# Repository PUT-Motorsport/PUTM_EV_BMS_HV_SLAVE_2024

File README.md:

# PUTM_EV_BMS_HV_SLAVE_2024
Accumulator Managment System (High Voltage Battery Managment System)

## Overview
The AMS system consists of two main parts, the master and multiple slaves.

The apparatus is responsible for the managment of the battery as a whole, determining it's states like: state of charge or unsafe state plausibility. It also supervises the turning on and off of the hv bus.

## Slave
The AMS Slave is a subsidiary system responsible for measuring all the cell voltages and strategically placed temperatures on one stack.

### Hardware 
The AMS Slave is powered by LTC6811, a powerful, new gen IC capable of measuring of up to 12 cell simultaneously and up to 5 auxilary readings. One slave features 2 of such IC for a total of 20 cell and 10 temperature measurements. All Slaves are connected in chain configuration allowing for a quick data dump from all slaves in series. For interfacing the LTC6811 uses isoSPI, a special SPI/Ethernet like protocol, which features amazing noise immunity due to usage of a twisted differential pair. All of that on a custom 4 layer board. The AMS slave boasts a lot smaller (106mm x 50mm) size compared to it's predecessor allowing for a lot more versatile usage and making one cell stack far more compact. 

### The research and development work was carried out was a part of the Student Scientific Clubs Create Innovations (SKNTI) program. [Ministry of Science and Higher Education](https://www.gov.pl/web/nauka)

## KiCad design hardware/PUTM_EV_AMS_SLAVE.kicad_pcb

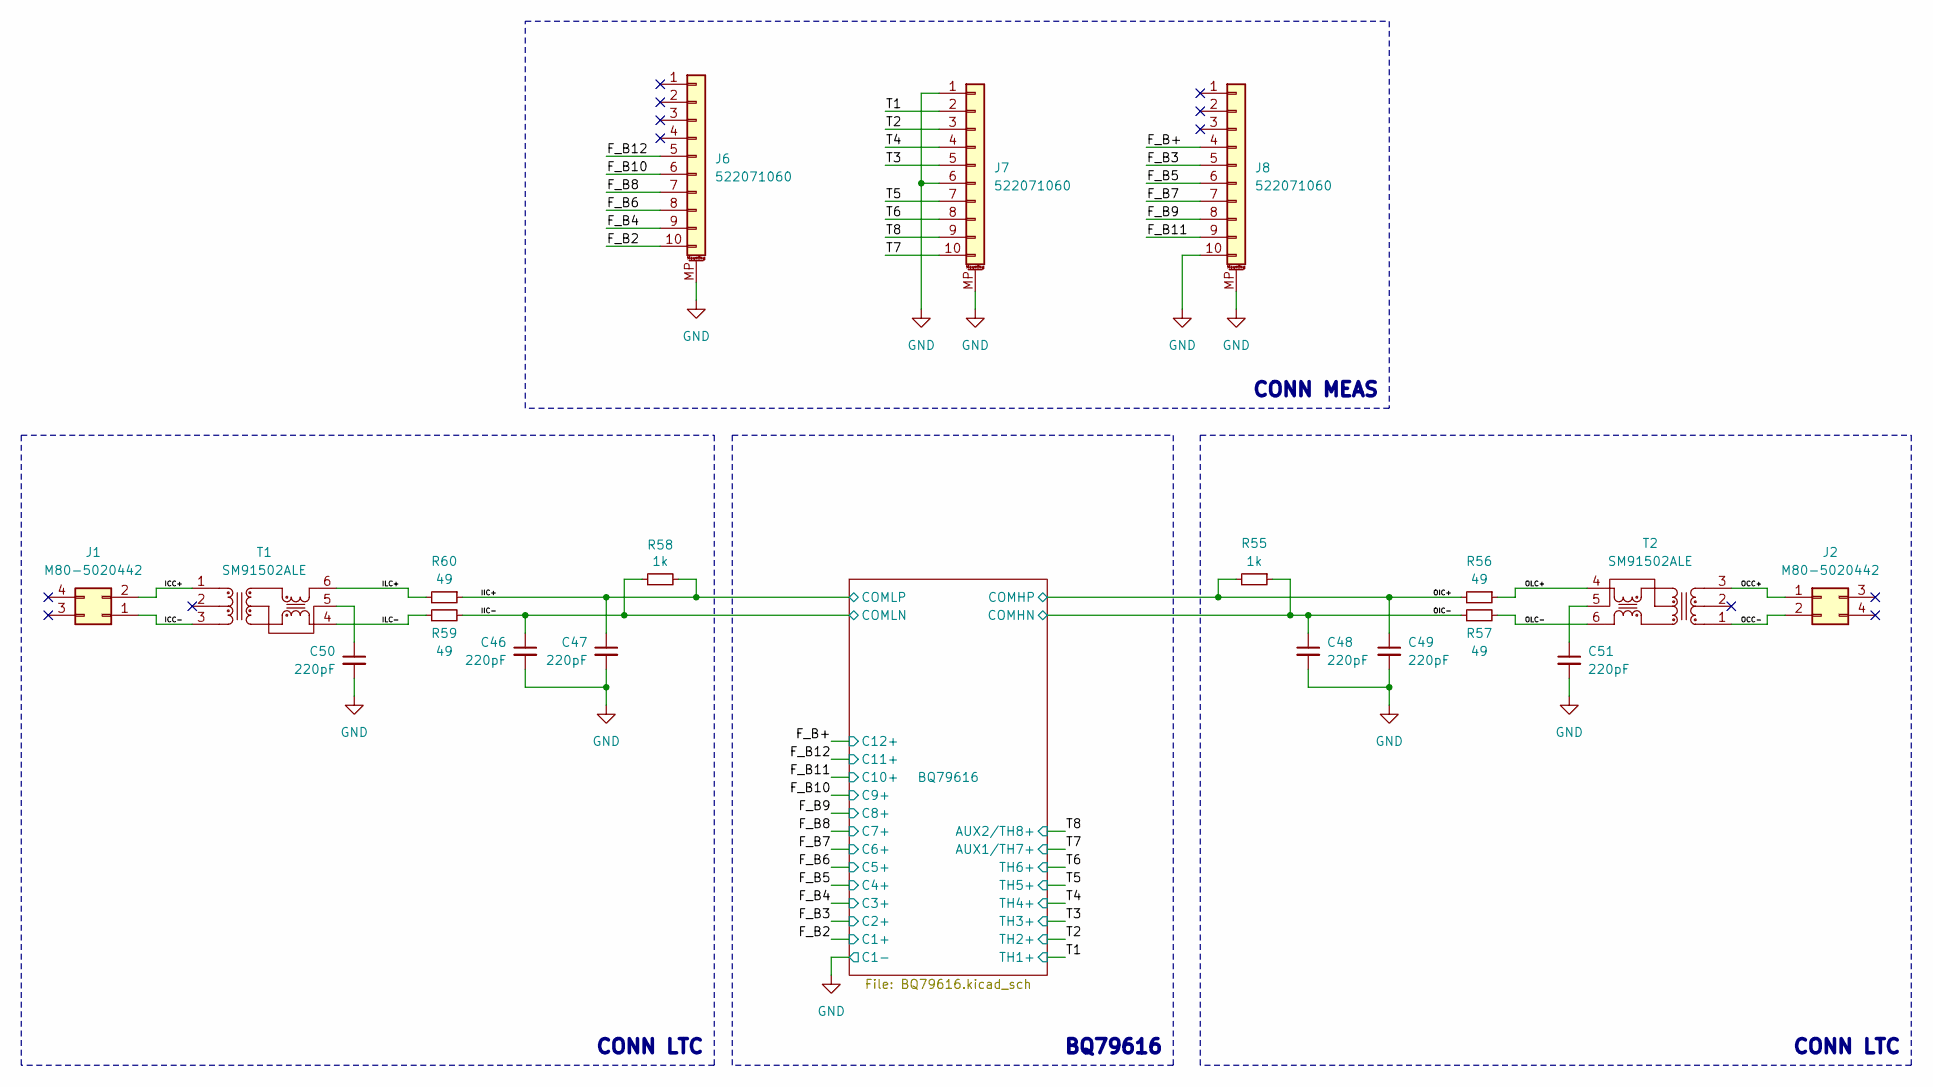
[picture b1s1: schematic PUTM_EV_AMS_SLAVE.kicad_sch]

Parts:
C46, C47, C48, C49, C50, C51: 220pF; C_0603_1608Metric; Mouser Part Number 581-06033A221JAT2A
J1, J2: M80-5020442; M80-50204YY; Mouser Part Number 855-M80-5020442
J6, J7, J8: 522071060; Mouser Part Number 538-52207-1060
R55, R58: 1k; R_0603_1608Metric; Manufacturer_Part_Number RT0603FRE07330RL; Mouser Part Number --
R56, R57, R59, R60: 49; R_0603_1608Metric; Manufacturer_Part_Number RT0603FRE07330RL; Mouser Part Number 603-RT0603FRE07330RL
T1, T2: SM91502ALE; SOP254P927X572-6N; Mouser Part Number 652-SM91502ALE

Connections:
/F_B2: J6.10; also elsewhere on the board
/F_B3: J8.5; also elsewhere on the board
/F_B4: J6.9; also elsewhere on the board
/F_B5: J8.6; also elsewhere on the board
/F_B6: J6.8; also elsewhere on the board
/F_B7: J8.7; also elsewhere on the board
/F_B8: J6.7; also elsewhere on the board
/F_B9: J8.8; also elsewhere on the board
/F_B10: J6.6; also elsewhere on the board
/F_B11: J8.9; also elsewhere on the board
/F_B12: J6.5; also elsewhere on the board
/F_B+: J8.4; also elsewhere on the board
/ICC+: J1.2, T1.1 (PRI_1)
/ICC-: J1.1, T1.3 (PRI_3)
/IIC+: C47.1, R58.2, R60.1; also elsewhere on the board
/IIC-: C46.1, R58.1, R59.2; also elsewhere on the board
/ILC+: R60.2, T1.6 (SEC_3)
/ILC-: R59.1, T1.4 (SEC_1)
/OCC+: J2.1, T2.3 (PRI_3)
/OCC-: J2.2, T2.1 (PRI_1)
/OIC+: C49.1, R55.2, R56.2; also elsewhere on the board
/OIC-: C48.1, R55.1, R57.1; also elsewhere on the board
/OLC+: R56.1, T2.4 (SEC_1)
/OLC-: R57.2, T2.6 (SEC_3)
/T1: J7.2; also elsewhere on the board
/T2: J7.3; also elsewhere on the board
/T3: J7.5; also elsewhere on the board
/T4: J7.4; also elsewhere on the board
/T5: J7.7; also elsewhere on the board
/T6: J7.8; also elsewhere on the board
/T7: J7.10; also elsewhere on the board
/T8: J7.9; also elsewhere on the board
GND: C46.2, C47.2, C48.2, C49.2, C50.2, C51.2, J6.MP (MountPin), J7.1, J7.6, J7.MP (MountPin), J8.10, J8.MP (MountPin); also elsewhere on the board
unnamed: C50.1, T1.5 (SEC_2)
unnamed: C51.1, T2.5 (SEC_2)

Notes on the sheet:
BQ79616
CONN LTC
CONN MEAS

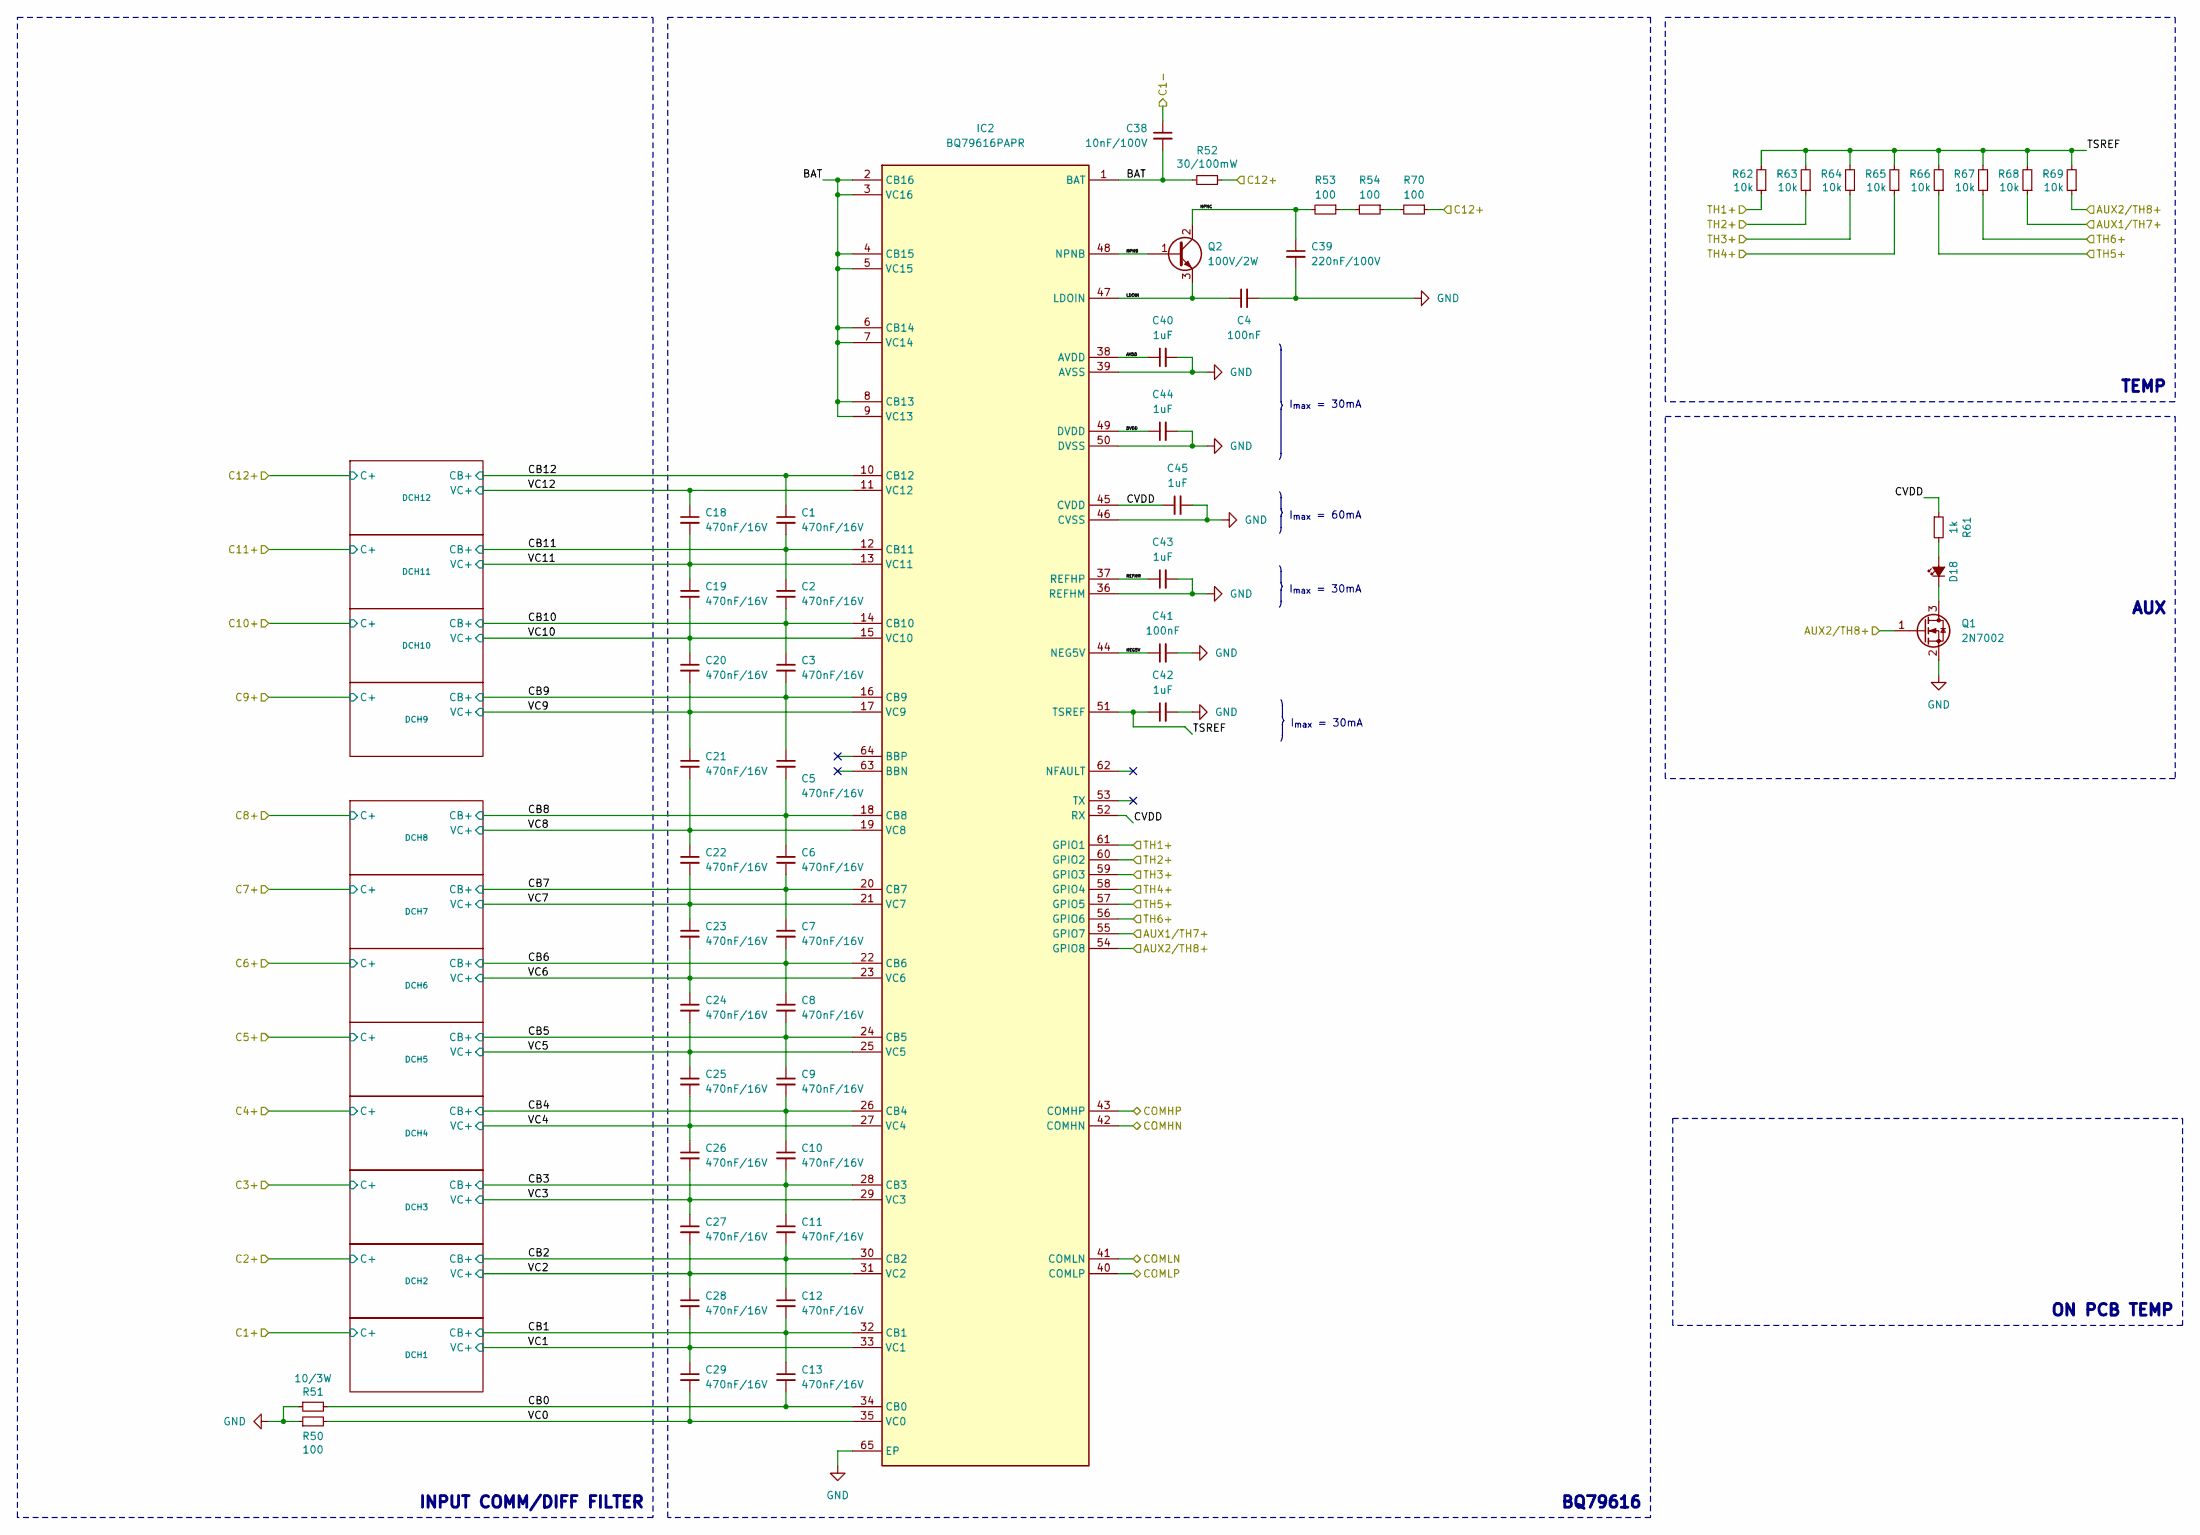
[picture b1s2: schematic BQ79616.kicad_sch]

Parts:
C1, C2, C3, C5, C6, C7, C8, C9, C10, C11, C12, C13, C18, C19, C20, C21, C22, C23, C24, C25, C26, C27, C28, C29: 470nF/16V; C_0603_1608Metric; Mouser Part Number 963-TMK107B7474KA-TR
C4, C41: 100nF; C_0603_1608Metric; Mouser Part Number --
C38: 10nF/100V; C_0603_1608Metric; Mouser Part Number 81-GRT188R72A103KE1J
C39: 220nF/100V; C_0805_2012Metric; Mouser Part Number 963-H168SC7224KTCA1J
C40, C42, C43, C44, C45: 1uF; C_0603_1608Metric; Mouser Part Number 187-CL10B105KA8NNNL
D18: LED; LED_0603_1608Metric; Manufacturer_Part_Number 150060SS75000; Mouser Part Number 710-150060SS75000
IC2: BQ79616PAPR; QFP50P1200X1200X120-65N; Mouser Part Number 595-BQ79616PAPR
Q1: 2N7002; SOT-23
Q2: 100V/2W; SOT-223-3_TabPin2; Mouser Part Number 522-FZT653TA
R50, R53, R54, R70: 100; R_0603_1608Metric; Manufacturer_Part_Number RT0603FRE07330RL; Mouser Part Number --
R51: 10/3W; R_2512_6332Metric; Manufacturer_Part_Number 352210RJT; Mouser Part Number 279-352210RJT
R52: 30/100mW; R_0603_1608Metric; Manufacturer_Part_Number RT0603FRE07330RL; Mouser Part Number 603-RT0603FRE07330RL
R61: 1k; R_0603_1608Metric; Manufacturer_Part_Number RT0603FRE07330RL; Mouser Part Number --
R62, R63, R64, R65, R66, R67, R68, R69: 10k; R_0603_1608Metric; Manufacturer_Part_Number RT0603FRE07330RL; Mouser Part Number --

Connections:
/BQ79616/AVDD: C40.1, IC2.38 (AVDD)
/BQ79616/BAT: C38.2, IC2.1 (BAT), IC2.2 (CB16), IC2.3 (VC16), IC2.4 (CB15), IC2.5 (VC15), IC2.6 (CB14), IC2.7 (VC14), IC2.8 (CB13), IC2.9 (VC13), R52.2
/BQ79616/CB0: C13.2, IC2.34 (CB0), R51.2
/BQ79616/CB1: C12.2, C13.1, IC2.32 (CB1); also elsewhere on the board
/BQ79616/CB2: C11.2, C12.1, IC2.30 (CB2); also elsewhere on the board
/BQ79616/CB3: C10.2, C11.1, IC2.28 (CB3); also elsewhere on the board
/BQ79616/CB4: C9.2, C10.1, IC2.26 (CB4); also elsewhere on the board
/BQ79616/CB5: C8.2, C9.1, IC2.24 (CB5); also elsewhere on the board
/BQ79616/CB6: C7.2, C8.1, IC2.22 (CB6); also elsewhere on the board
/BQ79616/CB7: C6.2, C7.1, IC2.20 (CB7); also elsewhere on the board
/BQ79616/CB8: C5.2, C6.1, IC2.18 (CB8); also elsewhere on the board
/BQ79616/CB9: C3.2, C5.1, IC2.16 (CB9); also elsewhere on the board
/BQ79616/CB10: C2.2, C3.1, IC2.14 (CB10); also elsewhere on the board
/BQ79616/CB11: C1.2, C2.1, IC2.12 (CB11); also elsewhere on the board
/BQ79616/CB12: C1.1, IC2.10 (CB12); also elsewhere on the board
/BQ79616/CVDD: C45.1, IC2.45 (CVDD), IC2.52 (RX), R61.1
/BQ79616/DVDD: C44.1, IC2.49 (DVDD)
/BQ79616/LDOIN: C4.1, IC2.47 (LDOIN), Q2.3 (E)
/BQ79616/NEG5V: C41.1, IC2.44 (NEG5V)
/BQ79616/NPNB: IC2.48 (NPNB), Q2.1 (B)
/BQ79616/NPNC: C39.1, Q2.2 (C), R53.2
/BQ79616/REFHM: C43.1, IC2.37 (REFHP)
/BQ79616/TSREF: C42.1, IC2.51 (TSREF), R62.2, R63.2, R64.2, R65.2, R66.2, R67.2, R68.2, R69.2
/BQ79616/VC0: C29.2, IC2.35 (VC0), R50.2
/BQ79616/VC1: C28.2, C29.1, IC2.33 (VC1); also elsewhere on the board
/BQ79616/VC2: C27.2, C28.1, IC2.31 (VC2); also elsewhere on the board
/BQ79616/VC3: C26.2, C27.1, IC2.29 (VC3); also elsewhere on the board
/BQ79616/VC4: C25.2, C26.1, IC2.27 (VC4); also elsewhere on the board
/BQ79616/VC5: C24.2, C25.1, IC2.25 (VC5); also elsewhere on the board
/BQ79616/VC6: C23.2, C24.1, IC2.23 (VC6); also elsewhere on the board
/BQ79616/VC7: C22.2, C23.1, IC2.21 (VC7); also elsewhere on the board
/BQ79616/VC8: C21.2, C22.1, IC2.19 (VC8); also elsewhere on the board
/BQ79616/VC9: C20.2, C21.1, IC2.17 (VC9); also elsewhere on the board
/BQ79616/VC10: C19.2, C20.1, IC2.15 (VC10); also elsewhere on the board
/BQ79616/VC11: C18.2, C19.1, IC2.13 (VC11); also elsewhere on the board
/BQ79616/VC12: C18.1, IC2.11 (VC12); also elsewhere on the board
/F_B+: R52.1, R70.1; also elsewhere on the board
/IIC+: IC2.40 (COMLP); also elsewhere on the board
/IIC-: IC2.41 (COMLN); also elsewhere on the board
/OIC+: IC2.43 (COMHP); also elsewhere on the board
/OIC-: IC2.42 (COMHN); also elsewhere on the board
/T1: IC2.61 (GPIO1), R62.1; also elsewhere on the board
/T2: IC2.60 (GPIO2), R63.1; also elsewhere on the board
/T3: IC2.59 (GPIO3), R64.1; also elsewhere on the board
/T4: IC2.58 (GPIO4), R65.1; also elsewhere on the board
/T5: IC2.57 (GPIO5), R66.1; also elsewhere on the board
/T6: IC2.56 (GPIO6), R67.1; also elsewhere on the board
/T7: IC2.55 (GPIO7), R68.1; also elsewhere on the board
/T8: IC2.54 (GPIO8), Q1.1 (G), R69.1; also elsewhere on the board
GND: C4.2, C38.1, C39.2, C40.2, C41.2, C42.2, C43.2, C44.2, C45.2, IC2.36 (REFHM), IC2.39 (AVSS), IC2.46 (CVSS), IC2.50 (DVSS), IC2.65 (EP), Q1.2 (S), R50.1, R51.1; also elsewhere on the board
unnamed: D18.2 (A), R61.2
unnamed: D18.1 (K), Q1.3 (D)
unnamed: R53.1, R54.2
unnamed: R54.1, R70.2

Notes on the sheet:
ON PCB TEMP
TEMP
BQ79616
AUX
I_{max} = 30mA
INPUT COMM/DIFF FILTER
I_{max} = 60mA

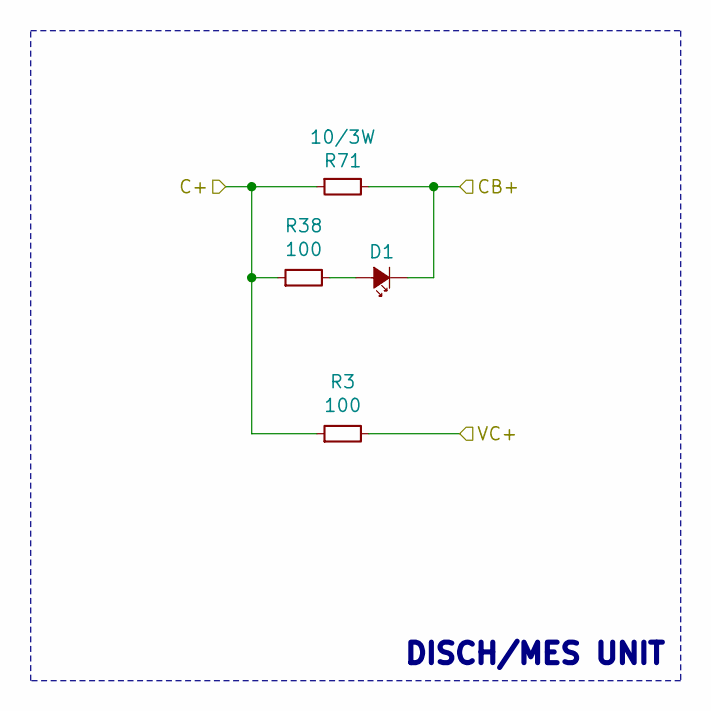
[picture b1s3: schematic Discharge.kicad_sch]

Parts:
D1: LED; LED_0603_1608Metric; Manufacturer_Part_Number 150060SS75000; Mouser Part Number 710-150060SS75000
R3, R38: 100; R_0603_1608Metric; Manufacturer_Part_Number RT0603FRE07330RL; Mouser Part Number --
R71: 10/3W; R_2512_6332Metric; Manufacturer_Part_Number 352210RJT; Mouser Part Number 279-352210RJT

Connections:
/BQ79616/CB1: D1.1 (K), R71.2; also elsewhere on the board
/BQ79616/VC1: R3.2; also elsewhere on the board
/F_B2: R3.1, R38.1, R71.1; also elsewhere on the board
unnamed: D1.2 (A), R38.2

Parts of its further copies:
D2, D3, D4, D5, D6, D7, D8, D9, D10, D11, D12: LED; LED_0603_1608Metric; Manufacturer_Part_Number 150060SS75000; Mouser Part Number 710-150060SS75000
R5, R8, R13, R16, R19, R22, R25, R28, R31, R34, R37, R39, R40, R41, R42, R43, R44, R45, R46, R47, R48, R49: 100; R_0603_1608Metric; Manufacturer_Part_Number RT0603FRE07330RL; Mouser Part Number --
R72, R73, R74, R75, R76, R77, R78, R79, R80, R81, R82: 10/3W; R_2512_6332Metric; Manufacturer_Part_Number 352210RJT; Mouser Part Number 279-352210RJT

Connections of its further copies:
/BQ79616/CB2: D2.1 (K), R72.2; also elsewhere on the board
/BQ79616/CB3: D3.1 (K), R73.2; also elsewhere on the board
/BQ79616/CB4: D4.1 (K), R74.2; also elsewhere on the board
/BQ79616/CB5: D5.1 (K), R75.2; also elsewhere on the board
/BQ79616/CB6: D6.1 (K), R76.2; also elsewhere on the board
/BQ79616/CB7: D7.1 (K), R77.2; also elsewhere on the board
/BQ79616/CB8: D8.1 (K), R78.2; also elsewhere on the board
/BQ79616/CB9: D9.1 (K), R79.2; also elsewhere on the board
/BQ79616/CB10: D10.1 (K), R80.2; also elsewhere on the board
/BQ79616/CB11: D11.1 (K), R81.2; also elsewhere on the board
/BQ79616/CB12: D12.1 (K), R82.2; also elsewhere on the board
/BQ79616/VC2: R5.2; also elsewhere on the board
/BQ79616/VC3: R8.2; also elsewhere on the board
/BQ79616/VC4: R13.2; also elsewhere on the board
/BQ79616/VC5: R16.2; also elsewhere on the board
/BQ79616/VC6: R19.2; also elsewhere on the board
/BQ79616/VC7: R22.2; also elsewhere on the board
/BQ79616/VC8: R25.2; also elsewhere on the board
/BQ79616/VC9: R28.2; also elsewhere on the board
/BQ79616/VC10: R31.2; also elsewhere on the board
/BQ79616/VC11: R34.2; also elsewhere on the board
/BQ79616/VC12: R37.2; also elsewhere on the board
/F_B3: R5.1, R39.1, R72.1; also elsewhere on the board
/F_B4: R8.1, R40.1, R73.1; also elsewhere on the board
/F_B5: R13.1, R41.1, R74.1; also elsewhere on the board
/F_B6: R16.1, R42.1, R75.1; also elsewhere on the board
/F_B7: R19.1, R43.1, R76.1; also elsewhere on the board
/F_B8: R22.1, R44.1, R77.1; also elsewhere on the board
/F_B9: R25.1, R45.1, R78.1; also elsewhere on the board
/F_B10: R28.1, R46.1, R79.1; also elsewhere on the board
/F_B11: R31.1, R47.1, R80.1; also elsewhere on the board
/F_B12: R34.1, R48.1, R81.1; also elsewhere on the board
/F_B+: R37.1, R49.1, R82.1; also elsewhere on the board
unnamed: D2.2 (A), R39.2
unnamed: D3.2 (A), R40.2
unnamed: D4.2 (A), R41.2
unnamed: D5.2 (A), R42.2
unnamed: D6.2 (A), R43.2
unnamed: D7.2 (A), R44.2
unnamed: D8.2 (A), R45.2
unnamed: D9.2 (A), R46.2
unnamed: D10.2 (A), R47.2
unnamed: D11.2 (A), R48.2
unnamed: D12.2 (A), R49.2

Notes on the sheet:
DISCH/MES UNIT

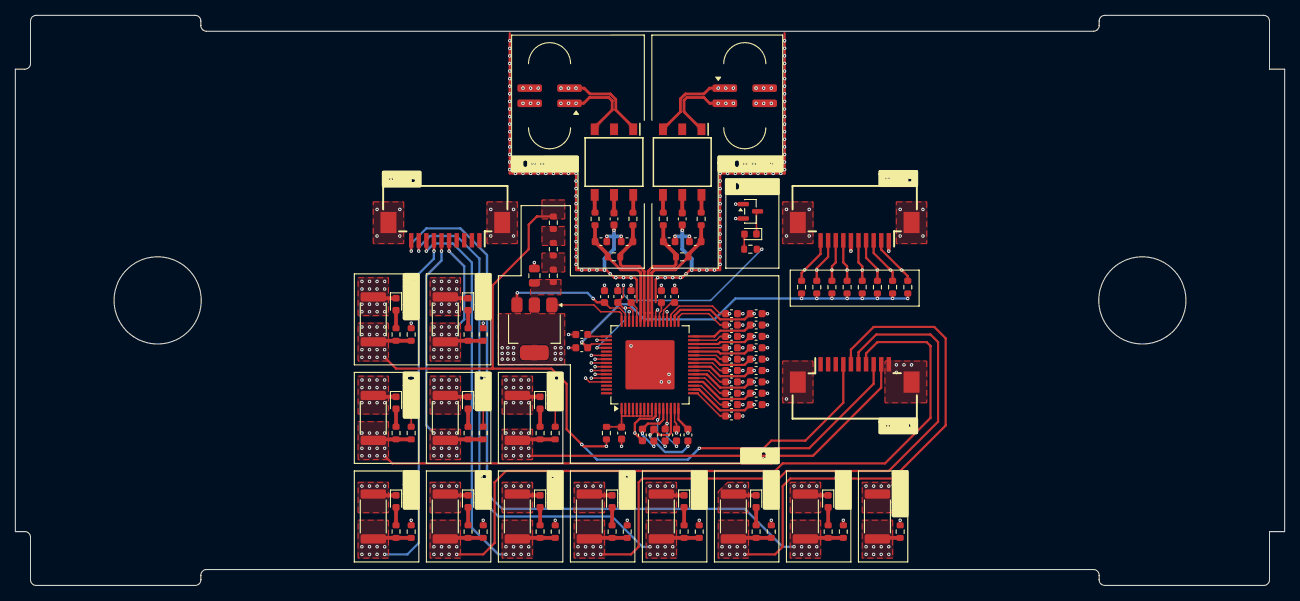
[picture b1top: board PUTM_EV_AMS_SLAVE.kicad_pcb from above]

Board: 4 copper layers, 167.4 x 75.2 mm, 119 parts (0 on the bottom side), 87 nets.

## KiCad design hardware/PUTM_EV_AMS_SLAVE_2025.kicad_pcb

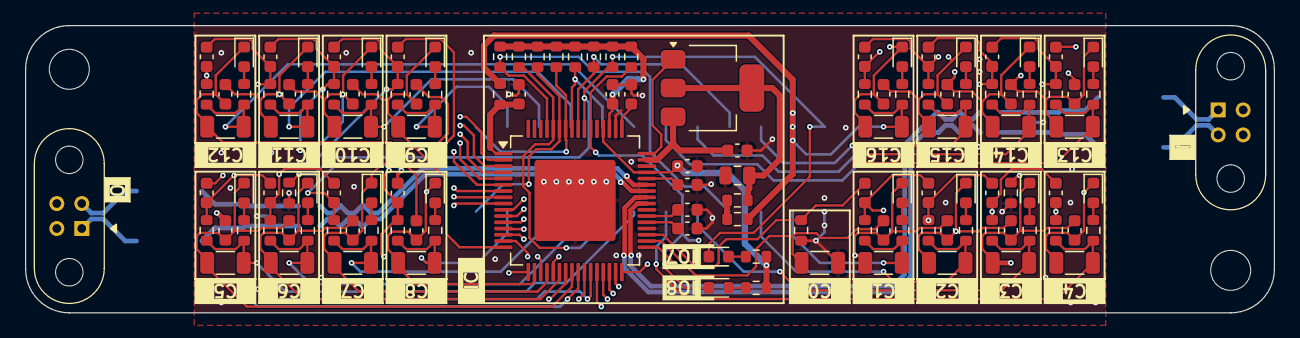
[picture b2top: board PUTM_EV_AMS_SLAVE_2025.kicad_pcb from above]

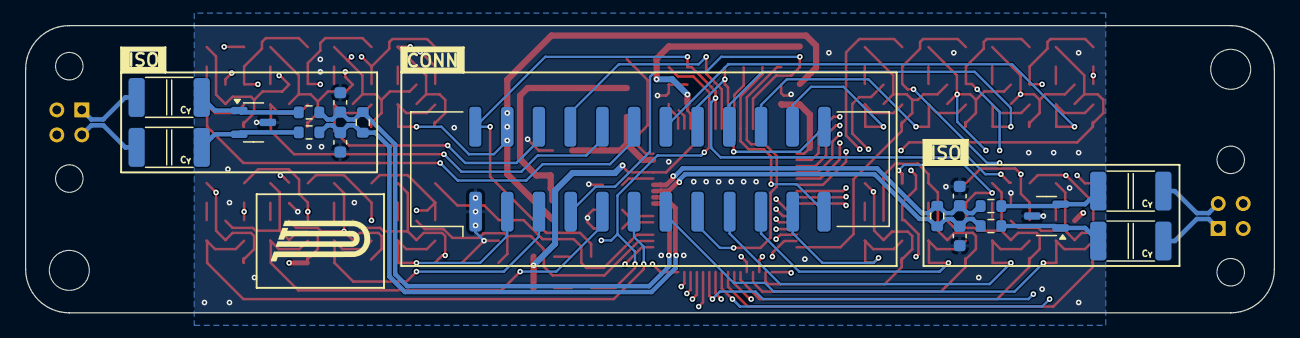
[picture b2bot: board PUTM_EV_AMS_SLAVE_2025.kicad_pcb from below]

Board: 4 copper layers, 100.0 x 23.0 mm, 145 parts (17 on the bottom side), 100 nets.

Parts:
C1, C2, C3, C9, C10, C11, C12, C13, C14, C15, C16, C17, C18, C19, C20, C21, C22, C23, C24, C25, C26, C27, C28, C29, C30, C31, C32, C33, C34, C35, C36, C37: 470nF/16V; C_0603_1608Metric
C4, C41: 100nF; C_0603_1608Metric
C5, C6, C7, C8: 4.7nF/Y2; CAPC5728X280N
C38: 10nF/100V; C_0603_1608Metric
C39: 220nF/100V; C_0805_2012Metric
C40, C42, C43, C44, C45: 1uF; C_0603_1608Metric
C46, C47, C48, C49: 220pF; C_0603_1608Metric
D1, D2, D3, D4, D5, D6, D7, D8, D9, D10, D11, D12, D13, D14, D15, D16, D17, D18: LED; LED_0603_1608Metric
D19, D20: 5.5V; SOT-23-3
IC2: BQ79616PAPR; QFP50P1200X1200X120-65N
J1, J2: M80-5100405; M80-51004YY
J4: IDC24; IDC-Header_2x12_P2.54mm_Vertical_SMD
Q2: 100V/2W; SOT-223-3_TabPin2
R1, R6, R10, R11, R14, R17, R20, R23, R26, R29, R32, R35, R38, R41, R44, R47: 330; R_0603_1608Metric
R2, R61, R62, R63, R64, R65, R66, R67, R68, R69: 10k; R_0603_1608Metric
R3, R5, R8, R13, R16, R19, R22, R25, R28, R31, R34, R37, R40, R43, R46, R49, R50, R53: 100; R_0603_1608Metric
R4, R7, R9, R12, R15, R18, R21, R24, R27, R30, R33, R36, R39, R42, R45, R48, R51: 33/1W; R_1206_3216Metric
R52: 30/100mW; R_0603_1608Metric
R54: 200; R_0603_1608Metric
R55, R58: 1k; R_0603_1608Metric
R56, R57, R59, R60: 49; R_0603_1608Metric
TH1, TH2: 10k/β=?; R_0603_1608Metric

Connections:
/AUX/TH7+: D17.1 (K), IC2.55 (GPIO7), J4.2, R68.1, TH1.1
/BQ79616/AUX2/TH8+: D18.1 (K), IC2.54 (GPIO8), R69.1, TH2.1
/BQ79616/AVDD: C40.1, IC2.38 (AVDD)
/BQ79616/BAT: C38.2, IC2.1 (BAT), R52.2
/BQ79616/CB0: C1.2, IC2.34 (CB0), R51.2
/BQ79616/CB1: C1.1, C2.2, D1.1 (K), IC2.32 (CB1), R9.2
/BQ79616/CB2: C2.1, C9.2, D2.1 (K), IC2.30 (CB2), R4.2
/BQ79616/CB3: C9.1, C11.2, D3.1 (K), IC2.28 (CB3), R7.2
/BQ79616/CB4: C11.1, C13.2, D4.1 (K), IC2.26 (CB4), R12.2
/BQ79616/CB5: C13.1, C15.2, D5.1 (K), IC2.24 (CB5), R15.2
/BQ79616/CB6: C15.1, C17.2, D6.1 (K), IC2.22 (CB6), R18.2
/BQ79616/CB7: C17.1, C20.2, D7.1 (K), IC2.20 (CB7), R21.2
/BQ79616/CB8: C20.1, C22.2, D8.1 (K), IC2.18 (CB8), R24.2
/BQ79616/CB9: C22.1, C24.2, D9.1 (K), IC2.16 (CB9), R27.2
/BQ79616/CB10: C24.1, C26.2, D10.1 (K), IC2.14 (CB10), R30.2
/BQ79616/CB11: C26.1, C28.2, D11.1 (K), IC2.12 (CB11), R33.2
/BQ79616/CB12: C28.1, C30.2, D12.1 (K), IC2.10 (CB12), R36.2
/BQ79616/CB13: C30.1, C32.2, D13.1 (K), IC2.8 (CB13), R39.2
/BQ79616/CB14: C32.1, C34.2, D14.1 (K), IC2.6 (CB14), R42.2
/BQ79616/CB15: C34.1, C36.2, D15.1 (K), IC2.4 (CB15), R45.2
/BQ79616/CB16: C36.1, D16.1 (K), IC2.2 (CB16), R48.2
/BQ79616/CVDD: C45.1, IC2.45 (CVDD), IC2.52 (RX), R2.1, R61.1
/BQ79616/DVDD: C44.1, IC2.49 (DVDD)
/BQ79616/LDOIN: C4.1, IC2.47 (LDOIN), Q2.3 (E)
/BQ79616/NEG5V: C41.1, IC2.44 (NEG5V)
/BQ79616/NPNB: IC2.48 (NPNB), Q2.1 (B)
/BQ79616/NPNC: C39.1, Q2.2 (C), R53.2
/BQ79616/REFHM: C43.1, IC2.37 (REFHP)
/BQ79616/TSREF: C42.1, IC2.51 (TSREF), R62.2, R63.2, R64.2, R65.2, R66.2, R67.2, R68.2, R69.2
/BQ79616/VC0: C18.2, IC2.35 (VC0), R50.2
/BQ79616/VC1: C3.2, C18.1, IC2.33 (VC1), R3.2
/BQ79616/VC2: C3.1, C10.2, IC2.31 (VC2), R5.2
/BQ79616/VC3: C10.1, C12.2, IC2.29 (VC3), R8.2
/BQ79616/VC4: C12.1, C14.2, IC2.27 (VC4), R13.2
/BQ79616/VC5: C14.1, C16.2, IC2.25 (VC5), R16.2
/BQ79616/VC6: C16.1, C19.2, IC2.23 (VC6), R19.2
/BQ79616/VC7: C19.1, C21.2, IC2.21 (VC7), R22.2
/BQ79616/VC8: C21.1, C23.2, IC2.19 (VC8), R25.2
/BQ79616/VC9: C23.1, C25.2, IC2.17 (VC9), R28.2
/BQ79616/VC10: C25.1, C27.2, IC2.15 (VC10), R31.2
/BQ79616/VC11: C27.1, C29.2, IC2.13 (VC11), R34.2
/BQ79616/VC12: C29.1, C31.2, IC2.11 (VC12), R37.2
/BQ79616/VC13: C31.1, C33.2, IC2.9 (VC13), R40.2
/BQ79616/VC14: C33.1, C35.2, IC2.7 (VC14), R43.2
/BQ79616/VC15: C35.1, C37.2, IC2.5 (VC15), R46.2
/BQ79616/VC16: C37.1, IC2.3 (VC16), R49.2
/C1+: J4.3, R3.1, R9.1, R10.1
/C2+: J4.5, R1.1, R4.1, R5.1
/C3+: J4.9, R6.1, R7.1, R8.1
/C4+: J4.11, R11.1, R12.1, R13.1
/C5+: J4.13, R14.1, R15.1, R16.1
/C6+: J4.17, R17.1, R18.1, R19.1
/C7+: J4.19, R20.1, R21.1, R22.1
/C8+: J4.21, R23.1, R24.1, R25.1
/C9+: J4.22, R26.1, R27.1, R28.1
/C10+: J4.20, R29.1, R30.1, R31.1
/C11+: J4.18, R32.1, R33.1, R34.1
/C12+: J4.14, R35.1, R36.1, R37.1
/C13+: J4.12, R38.1, R39.1, R40.1
/C14+: J4.10, R41.1, R42.1, R43.1
/C15+: J4.6, R44.1, R45.1, R46.1
/C16+: J4.4, R47.1, R48.1, R49.1, R52.1, R54.1
/ICC+: C8.1, J2.1
/ICC-: C7.1, J2.2
/IIC+: C46.1, IC2.40 (COMLP), R58.1, R59.2
/IIC-: C47.1, IC2.41 (COMLN), R58.2, R60.1
/ILC+: C8.2, D20.1 (K), R59.1
/ILC-: C7.2, D20.2 (K), R60.2
/OCC+: C5.2, J1.2
/OCC-: C6.2, J1.1
/OIC+: C49.1, IC2.43 (COMHP), R55.2, R56.2
/OIC-: C48.1, IC2.42 (COMHN), R55.1, R57.1
/OLC+: C5.1, D19.2 (K), R56.1
/OLC-: C6.1, D19.1 (K), R57.2
/TH1+: IC2.61 (GPIO1), J4.7, R62.1
/TH2+: IC2.60 (GPIO2), J4.15, R63.1
/TH3+: IC2.59 (GPIO3), J4.23, R64.1
/TH4+: IC2.58 (GPIO4), J4.24, R65.1
/TH5+: IC2.57 (GPIO5), J4.16, R66.1
/TH6+: IC2.56 (GPIO6), J4.8, R67.1
GND: C4.2, C38.1, C39.2, C40.2, C41.2, C42.2, C43.2, C44.2, C45.2, C46.2, C47.2, C48.2, C49.2, D19.3 (A), D20.3 (A), IC2.36 (REFHM), IC2.39 (AVSS), IC2.46 (CVSS), IC2.50 (DVSS), IC2.65 (EP), J4.1, R50.1, R51.1, TH1.2, TH2.2
unnamed: D1.2 (A), R10.2
unnamed: D2.2 (A), R1.2
unnamed: D3.2 (A), R6.2
unnamed: D4.2 (A), R11.2
unnamed: D5.2 (A), R14.2
unnamed: D6.2 (A), R17.2
unnamed: D7.2 (A), R20.2
unnamed: D8.2 (A), R23.2
unnamed: D9.2 (A), R26.2
unnamed: D10.2 (A), R29.2
unnamed: D11.2 (A), R32.2
unnamed: D12.2 (A), R35.2
unnamed: D13.2 (A), R38.2
unnamed: D14.2 (A), R41.2
unnamed: D15.2 (A), R44.2
unnamed: D16.2 (A), R47.2
unnamed: D17.2 (A), R2.2
unnamed: D18.2 (A), R61.2
unnamed: R53.1, R54.2
